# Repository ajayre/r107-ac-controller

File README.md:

# R107/C107 Air Conditioning Controller

This is an AC controller for the original Mercedes-Benz R107/C107 manual climate control system. The original system is identified by four vertical levers.

The problem with the AC switch is the delicate capillary tube that senses the evaporator temperature. With age these become brittle and snap off while working on items in the central console. Once broken they are not repairable. Replacements are not available to purchase.

The aim of this project is to replace the Ranco electro-mechanical part of the AC switch with a modern electronic equivalent.

This work is copyright (C) Andrew Ayre 2021 and no commercial use is permitted.

USE AT YOUR OWN RISK. NO WARRANTY, EXPRESS OR IMPLIED.

## Prototype Hardware

The prototype uses the following hardware:

* Arduino Nano - https://www.arduino.cc/en/pmwiki.php?n=Main/ArduinoBoardNano
* Adafruit Thermocouple Amplifier MAX31855 breakout board - https://www.adafruit.com/product/269
* Adafruit Power Relay FeatherWing - https://www.adafruit.com/product/3191

## Development Tools

* Arduino IDE - https://www.arduino.cc/en/software
* Install Microsoft Visual Studio Community Edition 2017 - https://visualstudio.microsoft.com/vs/older-downloads/
* Install Visual Micro - https://marketplace.visualstudio.com/items?itemName=VisualMicro.ArduinoIDEforVisualStudio

## Custom Board

### Programming the Bootloader

Use the Arduino IDE, choose the ATmega328P and your ISP programmer (e.g. USBtinyISP). If you choose to power the board from the programmer then there is no need to provide power via USP or 12V. Connect to the six-pin ISP connector.

### Programming the Firmware

Set the target to 'ATmega328P (Arduino Nano)'.
Connect to the USB connector - it will appear on your PC as a COM port.
Remove the RUN jumper. Replace the jumper after programming.

### LED Operation

The LED will turn on when firmware execution starts. Note that there is a delay of around two or three seconds while the bootloader runs and the LED will be off during this time.

* LED off = power supply problem
* LED on solid = in the 'ready' state, waiting for AC to be turned on. Compressor and blower are off
* LED on with flash off every two seconds = hardware error or corrupted firmware
* LED continually flashing = error
* LED flashing twice = in the 'running' state, blower is on and compressor cycles as needed
* LED flashing three times = in the 'freeze protection' state, blower is on and compressor is off

### RUN Jumper

The RUN jumper should be inserted when the board is installed in a vehicle. It needs to be removed during programming. The purpose of the RUN jumper is to stop noise on the receive line from keeping the board in the bootloader mode and stopping firmware from executing.

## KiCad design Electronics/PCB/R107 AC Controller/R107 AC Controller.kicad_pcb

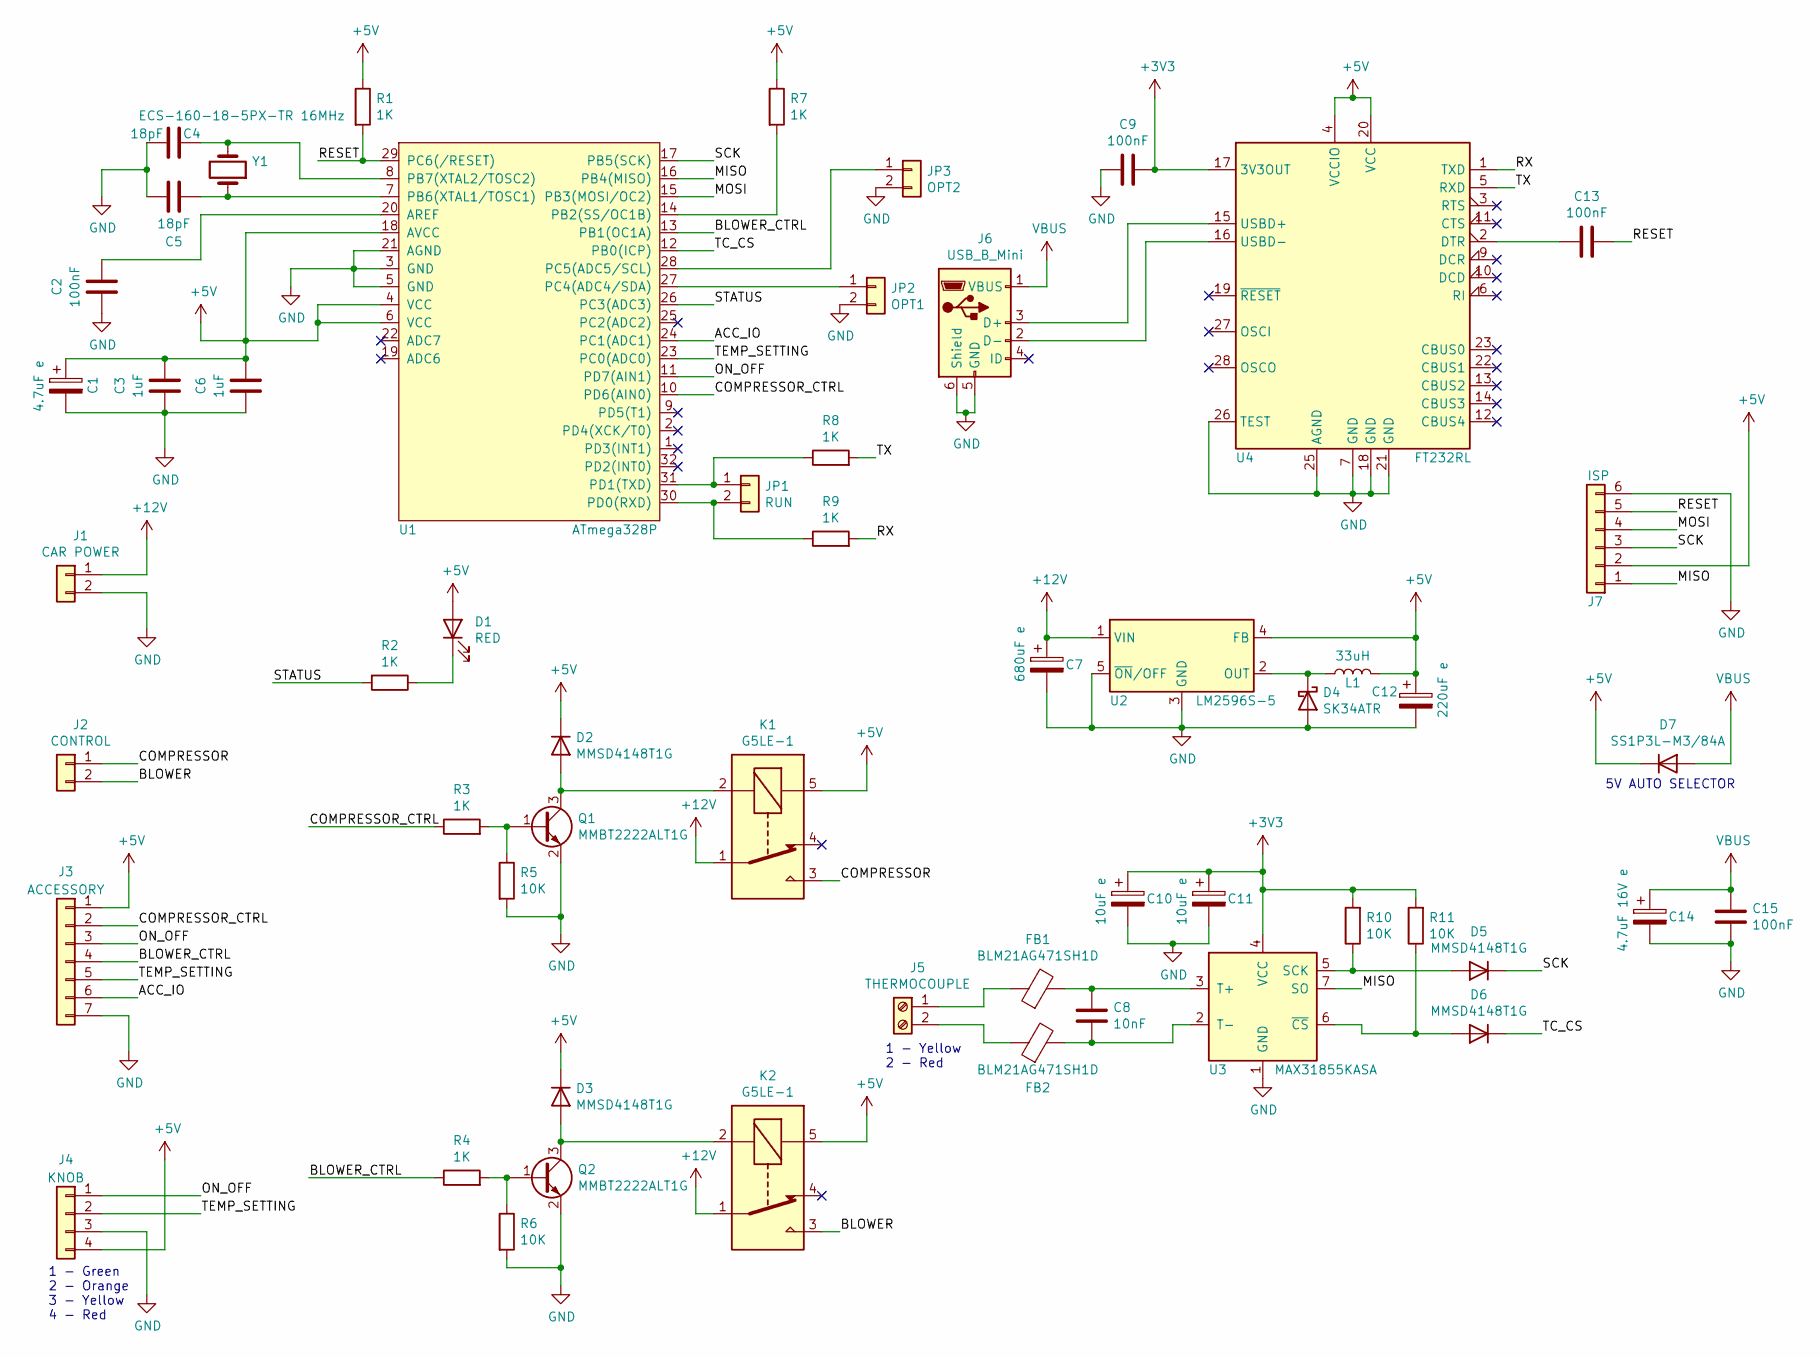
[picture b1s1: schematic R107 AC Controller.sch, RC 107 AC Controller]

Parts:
C1: 4.7uF e; CP_Elec_4x5.8
C2, C9, C13, C15: 100nF; C_0805_2012Metric
C3, C6: 1uF; C_0805_2012Metric
C4, C5: 18pF; C_0805_2012Metric
C7: 680uF e; CP_Elec_10x10.5
C8: 10nF; C_0805_2012Metric
C10, C11: 10uF e; CP_Elec_4x5.4
C12: 220uF e; CP_Elec_8x6.5
C14: 4.7uF 16V e; CP_Elec_4x5.8
D1: RED; LED_PLCC-2
D2, D3, D5, D6: MMSD4148T1G; D_SOD-123
D4: SK34ATR; D_SMA
D7: SS1P3L-M3/84A; SMP_DO-220AA
FB1, FB2: BLM21AG471SH1D; L_0805_2012Metric
J1: CAR POWER; Keystone_SturdiMount_TabConnector_1x2
J2: CONTROL; Keystone_SturdiMount_TabConnector_1x2
J3: ACCESSORY; PinHeader_1x07_P2.54mm_Vertical
J4: KNOB; Keystone_SturdiMount_TabConnector_1x4
J5: THERMOCOUPLE; TerminalBlock_TE_282834-2_1x02_P2.54mm_Horizontal
J6: USB_B_Mini; USB_Mini-B_Wuerth_65100516121_Horizontal
J7: ISP; PinHeader_2x03_P2.54mm_Vertical
JP1: RUN; PinHeader_1x02_P2.54mm_Vertical
JP2: OPT1; PinHeader_1x02_P2.54mm_Vertical
JP3: OPT2; PinHeader_1x02_P2.54mm_Vertical
K1, K2: G5LE-1; Relay_SPDT_Omron-G5LE-1
L1: 33uH; Chilisin_Power_Inductor_AWVS_808040
Q1, Q2: MMBT2222ALT1G; SOT-23
R1, R2, R3, R4, R7, R8, R9: 1K; R_0805_2012Metric
R5, R6, R10, R11: 10K; R_0805_2012Metric
U1: ATmega328P; LQFP-32_7x7mm_P0.8mm
U2: LM2596S-5; TO-263-5_TabPin3
U3: MAX31855KASA; SOIC-8_3.9x4.9mm_P1.27mm
U4: FT232RL; SSOP-28_5.3x10.2mm_P0.65mm
Y1: ECS-160-18-5PX-TR 16MHz; HC-49_US

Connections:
+3V3: C9.1, C10.1, C11.1, R10.2, R11.2, U3.4 (VCC), U4.17 (3V3OUT)
+5V: C1.1, C3.1, C6.1, C12.1, D1.2 (A), D2.1 (K), D3.1 (K), D7.1 (K), J3.1, J4.4, J7.2, K1.5, K2.5, L1.2, R1.1, R7.1, U1.4 (VCC), U1.6 (VCC), U1.18 (AVCC), U2.4 (FB), U4.4 (VCCIO), U4.20 (VCC)
+12V: C7.1, J1.1, K1.1, K2.1, U2.1 (VIN)
/ACC_IO: J3.6, U1.24 (PC1(ADC1))
/BLOWER: J2.2, K2.3
/BLOWER_CTRL: J3.4, R4.1, U1.13 (PB1(OC1A))
/COMPRESSOR: J2.1, K1.3
/COMPRESSOR_CTRL: J3.2, R3.1, U1.10 (PD6(AIN0))
/MISO: J7.1, U1.16 (PB4(MISO)), U3.7 (SO)
/MOSI: J7.4, U1.15 (PB3(MOSI/OC2))
/ON_OFF: J3.3, J4.1, U1.11 (PD7(AIN1))
/RESET: C13.1, J7.5, R1.2, U1.29 (PC6(/RESET))
/RX: R9.2, U4.1 (TXD)
/SCK: D5.1 (K), J7.3, U1.17 (PB5(SCK))
/STATUS: R2.2, U1.26 (PC3(ADC3))
/TC_CS: D6.1 (K), U1.12 (PB0(ICP))
/TEMP_SETTING: J3.5, J4.2, U1.23 (PC0(ADC0))
/TX: R8.2, U4.5 (RXD)
GND: C1.2, C2.2, C3.2, C4.2, C5.1, C6.2, C7.2, C9.2, C10.2, C11.2, C12.2, C14.2, C15.2, D4.2 (A), J1.2, J3.7, J4.3, J6.5 (GND), J6.6 (Shield), J7.6, JP2.2, JP3.2, Q1.2 (E), Q2.2 (E), R5.2, R6.2, U1.3 (GND), U1.5 (GND), U1.21 (AGND), U2.3 (GND), U2.5 (~ON~/OFF), U3.1 (GND), U4.7 (GND), U4.18 (GND), U4.21 (GND), U4.25 (AGND), U4.26 (TEST)
unnamed: C2.1, U1.20 (AREF)
unnamed: C4.1, U1.8 (PB7(XTAL2/TOSC2)), Y1.2
unnamed: C5.2, U1.7 (PB6(XTAL1/TOSC1)), Y1.1
unnamed: C8.1, FB2.2, U3.2 (T-)
unnamed: C8.2, FB1.2, U3.3 (T+)
unnamed: C13.2, U4.2 (DTR)
unnamed: D1.1 (K), R2.1
unnamed: D2.2 (A), K1.2, Q1.3 (C)
unnamed: D3.2 (A), K2.2, Q2.3 (C)
unnamed: D4.1 (K), L1.1, U2.2 (OUT)
unnamed: D5.2 (A), R10.1, U3.5 (SCK)
unnamed: D6.2 (A), R11.1, U3.6 (~CS~)
unnamed: FB1.1, J5.1
unnamed: FB2.1, J5.2
unnamed: J6.2 (D-), U4.16 (USBD-)
unnamed: J6.3 (D+), U4.15 (USBD+)
unnamed: JP1.1, R8.1, U1.31 (PD1(TXD))
unnamed: JP1.2, R9.1, U1.30 (PD0(RXD))
unnamed: JP2.1, U1.27 (PC4(ADC4/SDA))
unnamed: JP3.1, U1.28 (PC5(ADC5/SCL))
unnamed: Q1.1 (B), R3.2, R5.1
unnamed: Q2.1 (B), R4.2, R6.1
unnamed: R7.2, U1.14 (PB2(SS/OC1B))
VBUS: C14.1, C15.1, D7.2 (A), J6.1 (VBUS)

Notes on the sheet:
5V AUTO SELECTOR
1 - Green 2 - Orange 3 - Yellow 4 - Red
1 - Yellow 2 - Red

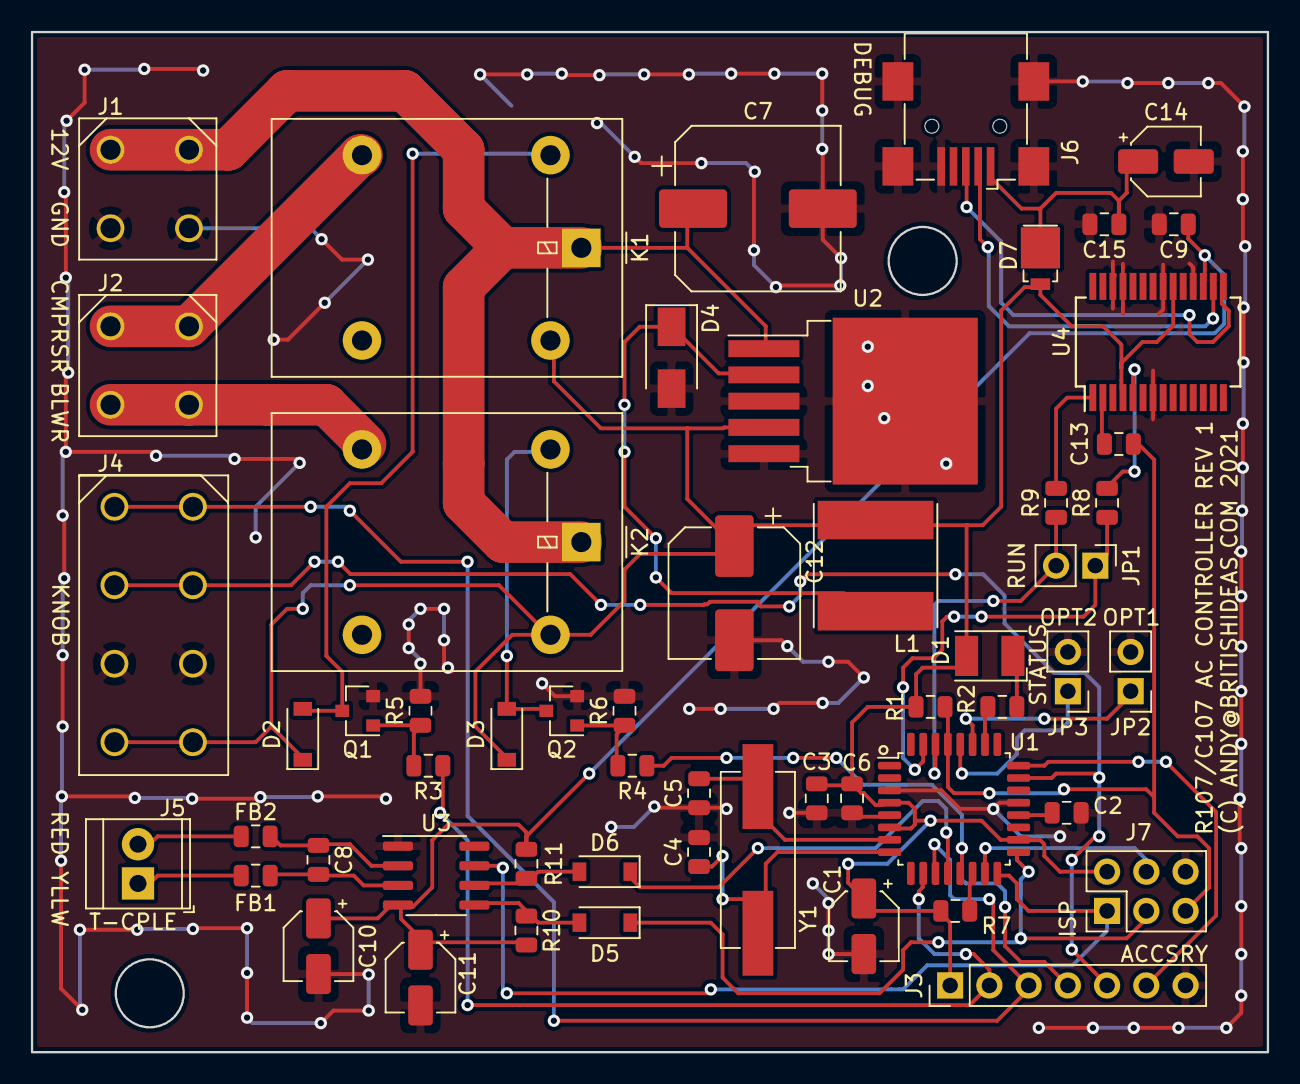
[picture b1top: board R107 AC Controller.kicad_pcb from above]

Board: 2 copper layers, 80.0 x 66.0 mm, 55 parts (0 on the bottom side), 43 nets.

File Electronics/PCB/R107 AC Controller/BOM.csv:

"Source:","C:\Users\andy\OneDrive\Documents\R107-AC-Controller\trunk\Electronics\PCB\R107 AC Controller\R107 AC Controller.sch"
"Date:","31/12/2020 14:29:16"
"Tool:","Eeschema (5.1.6)-1"
"Component Count:","55"
"Ref","Value","Footprint","Datasheet","Manufacturer","Vendor"
"C1","4.7uF e","Capacitor_SMD:CP_Elec_4x5.8","~","",""
"C2","100nF","Capacitor_SMD:C_0805_2012Metric","~","",""
"C3","1uF","Capacitor_SMD:C_0805_2012Metric","~","",""
"C4","18pF","Capacitor_SMD:C_0805_2012Metric","~","",""
"C5","18pF","Capacitor_SMD:C_0805_2012Metric","~","",""
"C6","1uF","Capacitor_SMD:C_0805_2012Metric","~","",""
"C7","680uF e","Capacitor_SMD:CP_Elec_10x10.5","~","",""
"C8","10nF","Capacitor_SMD:C_0805_2012Metric","~","",""
"C9","100nF","Capacitor_SMD:C_0805_2012Metric","~","",""
"C10","10uF e","Capacitor_SMD:CP_Elec_4x5.4","~","",""
"C11","10uF e","Capacitor_SMD:CP_Elec_4x5.4","~","",""
"C12","220uF e","Capacitor_SMD:CP_Elec_8x6.5","~","",""
"C13","100nF","Capacitor_SMD:C_0805_2012Metric","~","",""
"C14","4.7uF 16V e","Capacitor_SMD:CP_Elec_4x5.8","~","",""
"C15","100nF","Capacitor_SMD:C_0805_2012Metric","~","",""
"D1","RED","LED_SMD:LED_PLCC-2","~","",""
"D2","MMSD4148T1G","Diode_SMD:D_SOD-123","~","",""
"D3","MMSD4148T1G","Diode_SMD:D_SOD-123","~","",""
"D4","SK34ATR","Diode_SMD:D_SMA","~","",""
"D5","MMSD4148T1G","Diode_SMD:D_SOD-123","~","",""
"D6","MMSD4148T1G","Diode_SMD:D_SOD-123","~","",""
"D7","SS1P3L-M3/84A","Britishideas:SMP_DO-220AA","~","",""
"FB1","BLM21AG471SH1D","Inductor_SMD:L_0805_2012Metric","~","",""
"FB2","BLM21AG471SH1D","Inductor_SMD:L_0805_2012Metric","~","",""
"J1","CAR POWER","Britishideas:Keystone_SturdiMount_TabConnector_1x2","~","",""
"J2","CONTROL","Britishideas:Keystone_SturdiMount_TabConnector_1x2","~","",""
"J3","ACCESSORY","Connector_PinHeader_2.54mm:PinHeader_1x07_P2.54mm_Vertical","~","",""
"J4","KNOB","Britishideas:Keystone_SturdiMount_TabConnector_1x4","~","",""
"J5","THERMOCOUPLE","TerminalBlock_TE-Connectivity:TerminalBlock_TE_282834-2_1x02_P2.54mm_Horizontal","~","",""
"J6","USB_B_Mini","Connector_USB:USB_Mini-B_Wuerth_65100516121_Horizontal","~","",""
"J7","ISP","Connector_PinHeader_2.54mm:PinHeader_2x03_P2.54mm_Vertical","~","",""
"JP1","RUN","Connector_PinHeader_2.54mm:PinHeader_1x02_P2.54mm_Vertical","~","",""
"JP2","OPT1","Connector_PinHeader_2.54mm:PinHeader_1x02_P2.54mm_Vertical","~","",""
"JP3","OPT2","Connector_PinHeader_2.54mm:PinHeader_1x02_P2.54mm_Vertical","~","",""
"K1","G5LE-1","Relay_THT:Relay_SPDT_Omron-G5LE-1","http://www.omron.com/ecb/products/pdf/en-g5le.pdf","",""
"K2","G5LE-1","Relay_THT:Relay_SPDT_Omron-G5LE-1","http://www.omron.com/ecb/products/pdf/en-g5le.pdf","",""
"L1","33uH","Britishideas:Chilisin_Power_Inductor_AWVS_808040","~","",""
"Q1","MMBT2222ALT1G","Package_TO_SOT_SMD:SOT-23","~","",""
"Q2","MMBT2222ALT1G","Package_TO_SOT_SMD:SOT-23","~","",""
"R1","1K","Resistor_SMD:R_0805_2012Metric","~","",""
"R2","1K","Resistor_SMD:R_0805_2012Metric","~","",""
"R3","1K","Resistor_SMD:R_0805_2012Metric","~","",""
"R4","1K","Resistor_SMD:R_0805_2012Metric","~","",""
"R5","10K","Resistor_SMD:R_0805_2012Metric","~","",""
"R6","10K","Resistor_SMD:R_0805_2012Metric","~","",""
"R7","1K","Resistor_SMD:R_0805_2012Metric","~","",""
"R8","1K","Resistor_SMD:R_0805_2012Metric","~","",""
"R9","1K","Resistor_SMD:R_0805_2012Metric","~","",""
"R10","10K","Resistor_SMD:R_0805_2012Metric","~","",""
"R11","10K","Resistor_SMD:R_0805_2012Metric","~","",""
"U1","ATmega328P","Package_QFP:LQFP-32_7x7mm_P0.8mm","","",""
"U2","LM2596S-5","Package_TO_SOT_SMD:TO-263-5_TabPin3","http://www.ti.com/lit/ds/symlink/lm2596.pdf","",""
"U3","MAX31855KASA","Package_SO:SOIC-8_3.9x4.9mm_P1.27mm","http://datasheets.maximintegrated.com/en/ds/MAX31855.pdf","",""
"U4","FT232RL","Package_SO:SSOP-28_5.3x10.2mm_P0.65mm","https://www.ftdichip.com/Support/Documents/DataSheets/ICs/DS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","",""
"Y1","ECS-160-18-5PX-TR 16MHz","Britishideas:HC-49_US","~","",""

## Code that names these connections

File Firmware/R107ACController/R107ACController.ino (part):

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// size of temperature range controllable by user, in degrees celcius
#define TEMP_RANGE 15.0F

// pin to control the compressor
#define COMPRESSOR      6    // D6
// pin for on/off switch
#define CONTROL_SWITCH  7    // D7
// thermocouple chip select (uses hardware SPI)
#define CS_THERMOCOUPLE 8    // D8
// pin to control the blower motor
#define BLOWER_MOTOR    9    // D9
// pin for temperature control (analog)
#define TEMP_SETTING    A0
// pin for status LED
#define STATUS_LED      A3
// pin for opt 1
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#define IS_STATUS_LED_ON (digitalRead(STATUS_LED) == 1 ? FALSE : TRUE)

// blower control macros (connect to NO on relay)
#define BLOWER_OFF digitalWrite(BLOWER_MOTOR, LOW); Serial.println("Blower off");
#define BLOWER_ON  digitalWrite(BLOWER_MOTOR, HIGH); Serial.println("Blower on");
#define IS_BLOWER_ON digitalRead(BLOWER_MOTOR)

// compressor control macros (connect to NO on relay)
#define COMPRESSOR_OFF digitalWrite(COMPRESSOR, LOW); Serial.println("Compressor off")
#define COMPRESSOR_ON  digitalWrite(COMPRESSOR, HIGH); Serial.println("Compressor on")
#define IS_COMPRESSOR_ON digitalRead(COMPRESSOR)

// control switch macro
// returns 0 for off, 1 for on
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
// temp setting macro
// returns 0 = min, 1023 = max
#define RAW_TEMP_SETTING analogRead(TEMP_SETTING)
// raw temp setting where switch moves from fresh air to inside air
#define RAW_INSIDE_AIR_THRESHOLD 800
// scaled temp setting threshold
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  BLOWER_OFF;

  // configure compressor
  pinMode(COMPRESSOR, OUTPUT);
  COMPRESSOR_OFF;

  // configure control switch
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
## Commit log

2020-12-21 Added initial documents.
2020-12-21 Started code. Added Arduino nano pinout.
2020-12-21 Updated comments.
2020-12-23 Thermocouple now working.
2020-12-23 Working on state machine.
2020-12-23 Added more error checking.
2020-12-24 Added blower and compressor controls, untested. Added more debug output and some output cleanup.
2020-12-24 Added custom connectors.
2020-12-25 Added support for switch and pot. Removed unused connector.
2020-12-25 Added blower control to state machine. Code improvements. State machine improvements. Added state machine diagram (yED).
2020-12-25 Removed FAULT state.
2020-12-25 Added simulation of AC to test compressor cycling.
2020-12-25 Slowed down simulation. Bug fix to freeze protection.
2020-12-26 Added temperature control algorithm.
2020-12-26 Added datasheets and updated state machine diagram.
2020-12-26 Simplified target temperature calculation as the ambient temperature (outside air) is not known.
2020-12-27 Disabled simulation.
2020-12-27 First version of schematic diagram (requires KiCAD 5.1+). Added details of prototype setup.
2020-12-27 Updated schematic to fix mistakes.
2020-12-28 Added details of how to modify and wire the control knob.
2020-12-28 Renamed file.
2020-12-28 Updated control knob documentation.
2020-12-28 Fixed mistake in control knob schematic.
2020-12-29 Updated schematic. Added BOM. Added more data sheets.
2020-12-30 Improvements to schematic. Started work on PCB.
2020-12-31 Working on PCB. Added status LED and removed comms LEDs. Added jumper to reduce chances of noise on RX input keeping bootloader running.
2020-12-31 First attempt at PCB.
2020-12-31 Working on PCB. Adding 3D models. Moved silkscreen text away from vias where possible.
2020-12-31 Completed 3D models. Fixed mistake with footprint for L1 - was too small.
2020-12-31 Added render of board.
2020-12-31 Added CAD model of PCB for Alibre Design and STEP file. Added BOM.
2021-01-01 Added R107 silhouette to bottom of PCB.
2021-01-02 Added instructions for thermocouple. Updated pot bracket to work better with ABS plastic.
2021-01-03 Changed thermocouple connector to quick disconnect type.
2021-01-03 Added two pin connector for thermocouple. Removed one pin connector - not needed.
2021-01-04 Updated footprints for connectors. Generated gerber files.
2021-01-04 Updated readmes.
2021-01-04 Added PDF of schematic. Updated knob readme. Added pictures of knob.
2021-01-04 Removed two pin connector - not needed.
2021-01-04 Updated readme.
2021-01-04 Added firmware readme.
2021-01-04 Added KiCAD custom PCB footprints.
2021-01-04 Updated 3D model of board.
2021-01-05 Added specific pot used.
2021-01-05 Working on case.
2021-01-12 Added readme for case.
2021-01-12 Updated case readme.
2021-01-15 Enlarge bolt holes.
2021-01-15 Removed edge chamfer from case - wasn't noticeable in the print and just helps to make the corners curl.
2021-01-23 Minor silkscreen tweak. Updated part name for diode.
2021-01-24 Added additional datasheets. Updated schematic PDF.
2021-01-26 Regenerated BOM.
2021-01-31 Added support for LED.
2021-01-31 LED solid on when in ready state.
2021-01-31 Added PCB README. Changed part for diode D7.
2021-01-31 Updated BOM from Digikey.
2021-01-31 Added reading of option jumpers.
2021-02-01 Added moving average for temperature.
2021-02-01 Cleanup of debug output. Reduced watchdog timeout to two seconds. Improved evap temperature averaging. Controller does not use evap temperature that has not been averaged (an initial set of samples c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
2021-02-01 Updated knob readme.
2021-02-08 Better fit for PCB.
2021-02-14 Added images of Car Wiring.jpg
2021-02-14 Added Powerpoint source file for wiring annotations.
2021-02-17 Updated PDF schematic and BOM.
2021-03-06 Updated to current ATmega328P

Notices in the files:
Firmware/R107ACController/R107ACController.ino:
(C) Andy Ayre, 2021, all rights reserved, no commercial usage
Electronics/PCB/R107 AC Controller/R107 AC Controller.sch:
(C) 2020, For personal use only, no commercial use
